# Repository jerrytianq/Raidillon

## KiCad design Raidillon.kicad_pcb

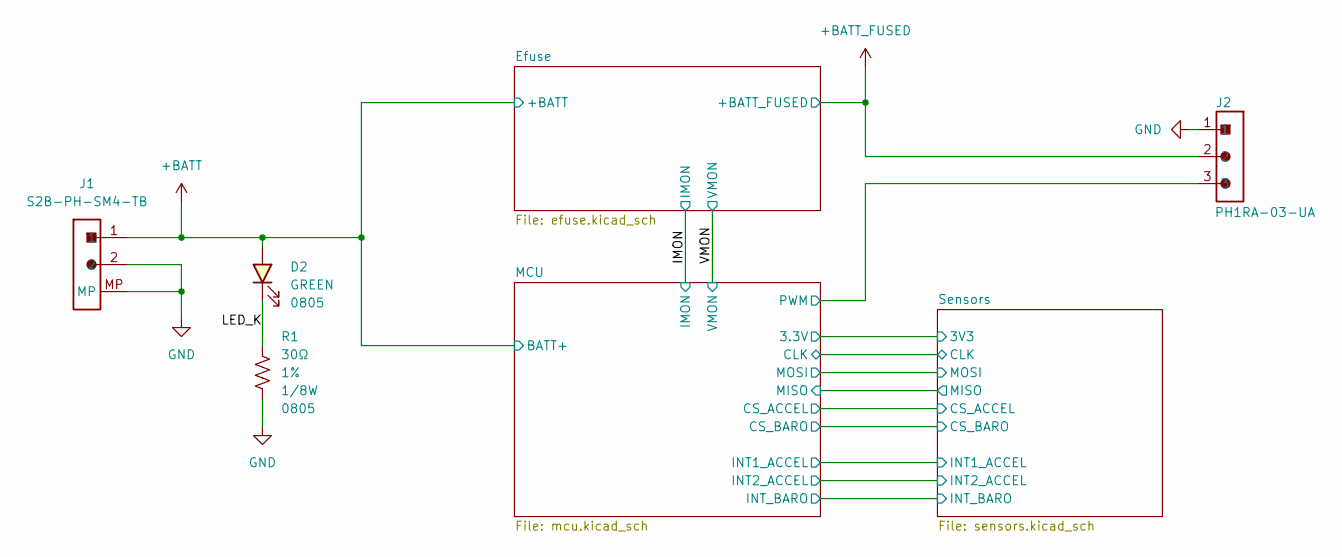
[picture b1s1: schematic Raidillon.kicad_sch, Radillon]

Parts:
D2: 150080GS75000; LED_0805_2012Metric_Pad1.15x1.40mm_HandSolder
J1: S2B-PH-SM4-TB; JST_PH_S2B-PH-SM4-TB_1x02-1MP_P2.00mm_Horizontal
J2: PH1RA-03-UA; PinHeader_1x03_P2.54mm_Horizontal
R1: RC0805FR-0730RL; R_0805_2012Metric_Pad1.20x1.40mm_HandSolder; Tolerance 1%

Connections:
+BATT: D2.2 (A), J1.1; also elsewhere on the board
+BATT_FUSED: J2.2; also elsewhere on the board
/LED_K: D2.1 (K), R1.1
/MCU/PWM: J2.3; also elsewhere on the board
GND: J1.2, J1.MP, J2.1, R1.2; also elsewhere on the board

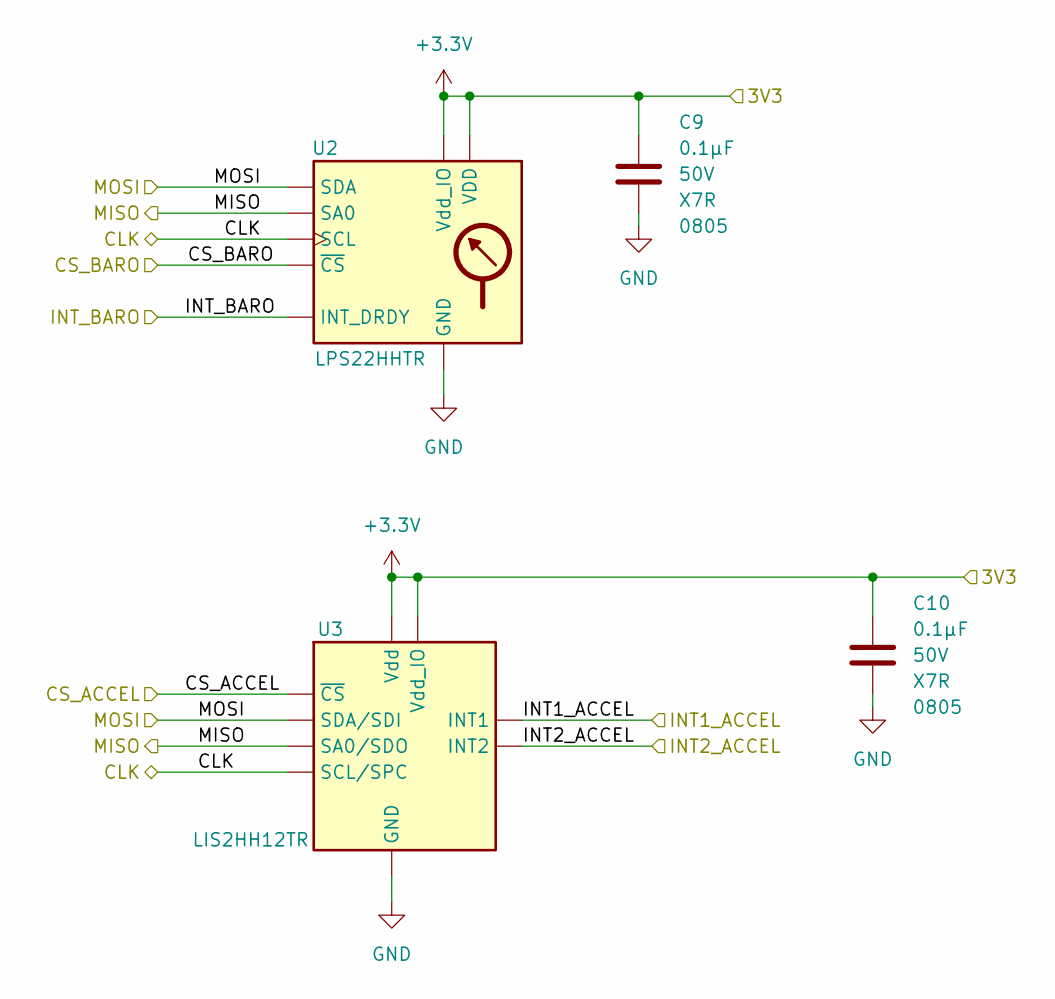
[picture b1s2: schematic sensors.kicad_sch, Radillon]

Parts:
C9, C10: CL21B104KBCNNNC; C_0805_2012Metric_Pad1.18x1.45mm_HandSolder; Rated Voltage 50V
U2: LPS22HHTR; ST_HLGA-10_LPS22HHTR
U3: LIS2HH12TR; LGA-12_LIS2HH12TR

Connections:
+3.3V: C9.1, C10.1, U2.1 (Vdd_IO), U2.10 (VDD), U3.9 (Vdd), U3.10 (Vdd_IO); also elsewhere on the board
/MCU/CLK: U2.2 (SCL), U3.1 (SCL/SPC); also elsewhere on the board
/MCU/CS_ACCEL: U3.2 (~CS); also elsewhere on the board
/MCU/CS_BARO: U2.6 (~CS); also elsewhere on the board
/MCU/INT1_ACCEL: U3.12 (INT1); also elsewhere on the board
/MCU/INT2_ACCEL: U3.11 (INT2); also elsewhere on the board
/MCU/INT_BARO: U2.7 (INT_DRDY); also elsewhere on the board
/MCU/MISO: U2.5 (SA0), U3.3 (SA0/SDO); also elsewhere on the board
/MCU/MOSI: U2.4 (SDA), U3.4 (SDA/SDI); also elsewhere on the board
GND: C9.2, C10.2, U2.3 (GND), U2.8 (GND), U2.9 (GND), U3.5 (RES), U3.6 (GND), U3.7 (GND), U3.8 (GND); also elsewhere on the board

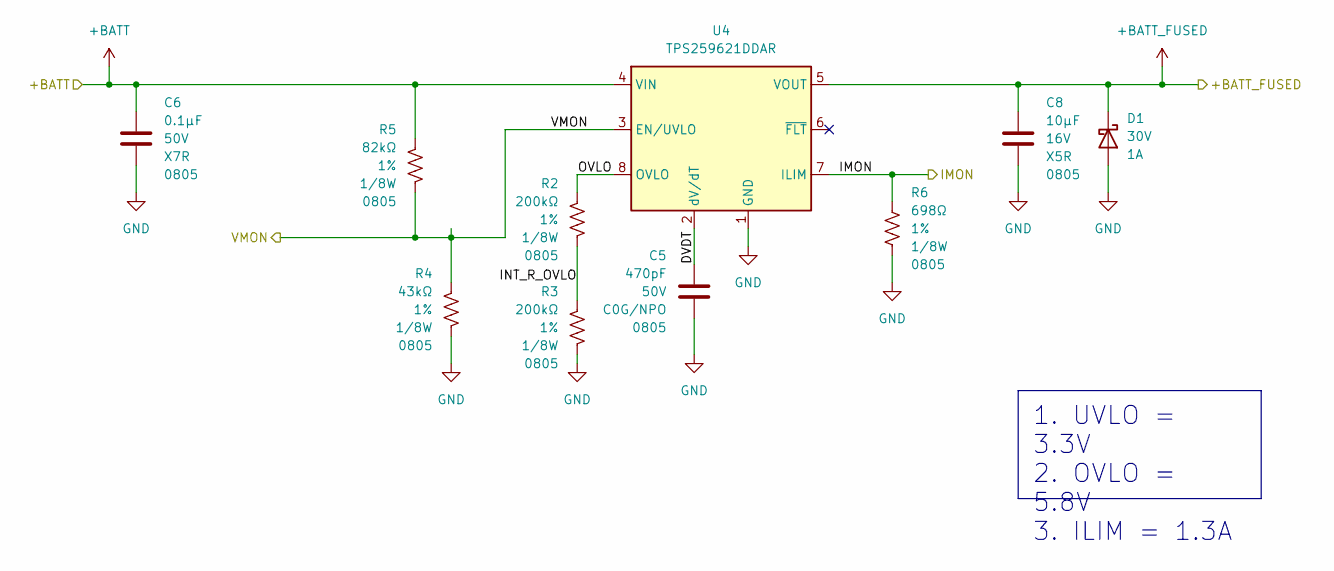
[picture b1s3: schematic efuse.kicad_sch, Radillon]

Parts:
C5: CC0805JRNPO9BN471; C_0805_2012Metric_Pad1.18x1.45mm_HandSolder; Rated Voltage 50V
C6: CL21B104KBCNNNC; C_0805_2012Metric_Pad1.18x1.45mm_HandSolder; Rated Voltage 50V
C8: GRM21BR61C106KE15K; C_0805_2012Metric_Pad1.18x1.45mm_HandSolder; Rated Voltage 16V
D1: MSS1P3L-M3/89A; D_MicroSMP_AK_MSS1P3L-M3_89A; Voltage - DC Reverse (V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 30V
R2, R3: RC0805FR-07200KL; R_0805_2012Metric_Pad1.20x1.40mm_HandSolder; Tolerance 1%
R4: RC0805FR-0743KL; R_0805_2012Metric_Pad1.20x1.40mm_HandSolder; Tolerance 1%
R5: RC0805FR-0782KL; R_0805_2012Metric_Pad1.20x1.40mm_HandSolder; Tolerance 1%
R6: RC0805FR-07698RL; R_0805_2012Metric_Pad1.20x1.40mm_HandSolder; Tolerance 1%
U4: TPS259621DDAR; SOIC-8-TPS259631DDAR; Voltage - Input 2.7V ~ 19V

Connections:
+BATT: C6.1, R5.1, U4.4 (VIN); also elsewhere on the board
+BATT_FUSED: C8.1, D1.1 (K), U4.5 (VOUT); also elsewhere on the board
/Efuse/DVDT: C5.1, U4.2 (dV/dT)
/Efuse/INT_R_OVLO: R2.2, R3.1
/Efuse/OVLO: R2.1, U4.8 (OVLO)
/IMON: R6.1, U4.7 (ILIM); also elsewhere on the board
/VMON: R4.1, R5.2, U4.3 (EN/UVLO); also elsewhere on the board
GND: C5.2, C6.2, C8.2, D1.2 (A), R3.2, R4.2, R6.2, U4.1 (GND), U4.9 (GND); also elsewhere on the board

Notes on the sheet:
1. UVLO = 3.3V 2. OVLO = 5.8V 3. ILIM = 1.3A

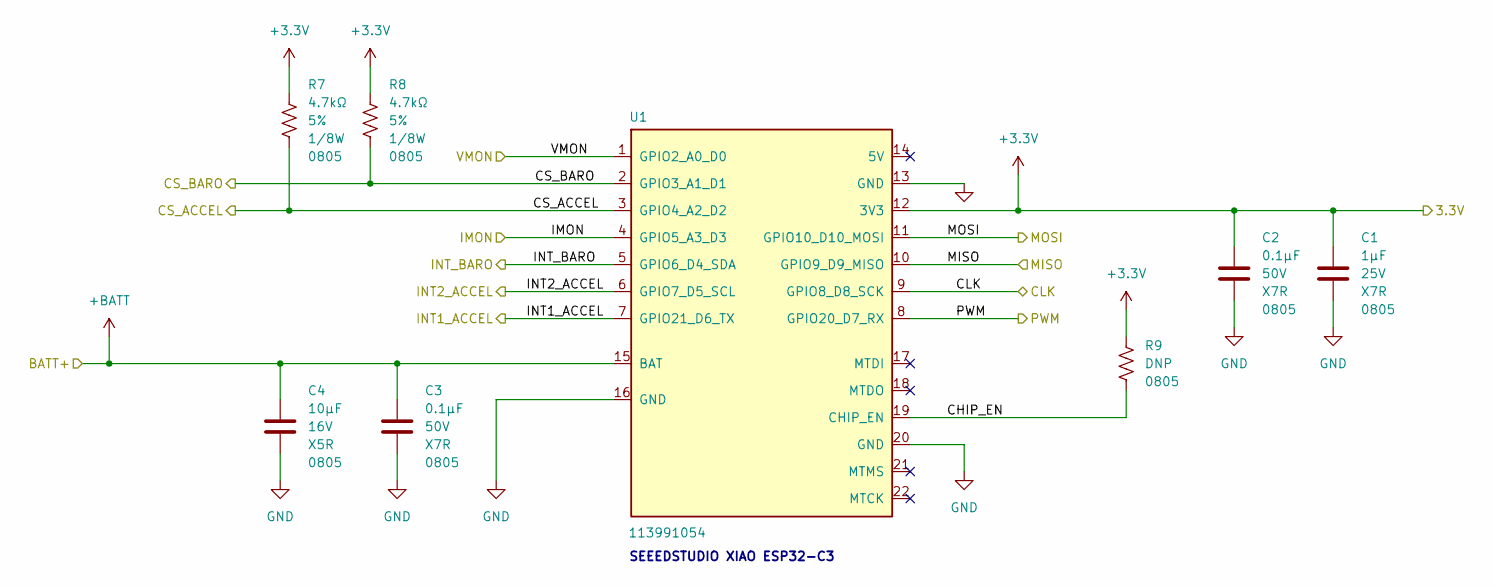
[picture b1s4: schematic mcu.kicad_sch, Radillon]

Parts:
C1: CL21B105KAFNNNE; C_0805_2012Metric_Pad1.18x1.45mm_HandSolder; Rated Voltage 25V
C2, C3: CL21B104KBCNNNC; C_0805_2012Metric_Pad1.18x1.45mm_HandSolder; Rated Voltage 50V
C4: GRM21BR61C106KE15K; C_0805_2012Metric_Pad1.18x1.45mm_HandSolder; Rated Voltage 16V
R7, R8: RMCF0805JT4K70; R_0805_2012Metric_Pad1.20x1.40mm_HandSolder; Tolerance 5%; PARTREV V.12
R9: DNP 0805; R_0805_2012Metric_Pad1.20x1.40mm_HandSolder; PARTREV V.12
U1: 113991054; XIAO-ESP32C3-SMD

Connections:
+3.3V: C1.1, C2.1, R7.1, R8.1, R9.1, U1.12 (3V3); also elsewhere on the board
+BATT: C3.1, C4.1, U1.15 (BAT); also elsewhere on the board
/IMON: U1.4 (GPIO5_A3_D3); also elsewhere on the board
/MCU/CHIP_EN: R9.2, U1.19 (CHIP_EN)
/MCU/CLK: U1.9 (GPIO8_D8_SCK); also elsewhere on the board
/MCU/CS_ACCEL: R7.2, U1.3 (GPIO4_A2_D2); also elsewhere on the board
/MCU/CS_BARO: R8.2, U1.2 (GPIO3_A1_D1); also elsewhere on the board
/MCU/INT1_ACCEL: U1.7 (GPIO21_D6_TX); also elsewhere on the board
/MCU/INT2_ACCEL: U1.6 (GPIO7_D5_SCL); also elsewhere on the board
/MCU/INT_BARO: U1.5 (GPIO6_D4_SDA); also elsewhere on the board
/MCU/MISO: U1.10 (GPIO9_D9_MISO); also elsewhere on the board
/MCU/MOSI: U1.11 (GPIO10_D10_MOSI); also elsewhere on the board
/MCU/PWM: U1.8 (GPIO20_D7_RX); also elsewhere on the board
/VMON: U1.1 (GPIO2_A0_D0); also elsewhere on the board
GND: C1.2, C2.2, C3.2, C4.2, U1.13 (GND), U1.16 (GND), U1.20 (GND); also elsewhere on the board

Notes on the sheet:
SEEEDSTUDIO XIAO ESP32-C3

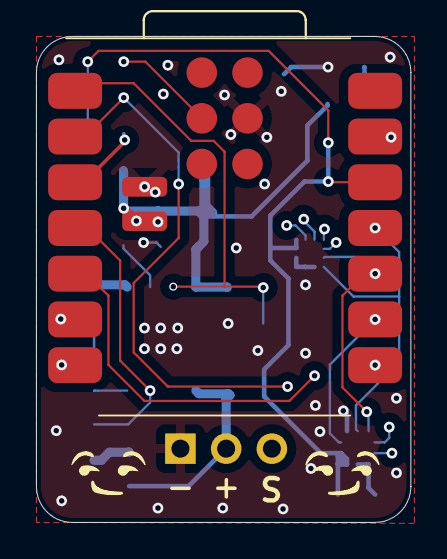
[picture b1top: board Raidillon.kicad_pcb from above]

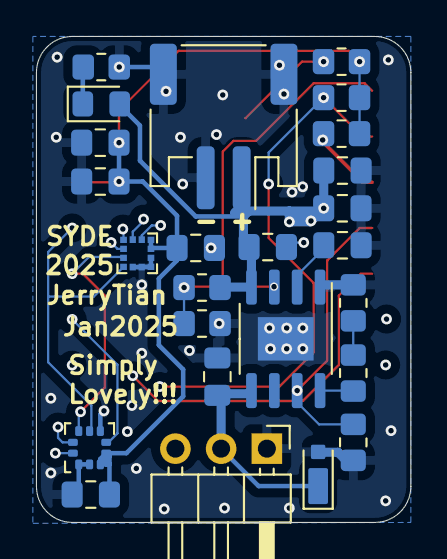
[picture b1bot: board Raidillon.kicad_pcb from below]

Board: 4 copper layers, 20.8 x 27.0 mm, 26 parts (25 on the bottom side), 20 nets.

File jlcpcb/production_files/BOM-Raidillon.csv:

Comment,Designator,Footprint,LCSC,Quantity
113991054,U1,XIAO-ESP32C3-SMD,,1
RMCF0805JT4K70,R8,R_0805_2012Metric_Pad1.20x1.40mm_HandSolder,,1
CL21B105KAFNNNE,C1,C_0805_2012Metric_Pad1.18x1.45mm_HandSolder,,1
RMCF0805JT4K70,R7,R_0805_2012Metric_Pad1.20x1.40mm_HandSolder,,1
CL21B104KBCNNNC,C9,C_0805_2012Metric_Pad1.18x1.45mm_HandSolder,,1
MSS1P3L-M3/89A,D1,D_MicroSMP_AK_MSS1P3L-M3_89A,,1
CL21B104KBCNNNC,C10,C_0805_2012Metric_Pad1.18x1.45mm_HandSolder,,1
RC0805FR-0730RL,R1,R_0805_2012Metric_Pad1.20x1.40mm_HandSolder,,1
GRM21BR61C106KE15K,C8,C_0805_2012Metric_Pad1.18x1.45mm_HandSolder,,1
GRM21BR61C106KE15K,C4,C_0805_2012Metric_Pad1.18x1.45mm_HandSolder,,1
CC0805JRNPO9BN471,C5,C_0805_2012Metric_Pad1.18x1.45mm_HandSolder,,1
150080GS75000,D2,LED_0805_2012Metric_Pad1.15x1.40mm_HandSolder,,1
CL21B104KBCNNNC,C3,C_0805_2012Metric_Pad1.18x1.45mm_HandSolder,,1
RC0805FR-0782KL,R5,R_0805_2012Metric_Pad1.20x1.40mm_HandSolder,,1
CL21B104KBCNNNC,C2,C_0805_2012Metric_Pad1.18x1.45mm_HandSolder,,1
DNP 0805,,R_0805_2012Metric_Pad1.20x1.40mm_HandSolder,,0
RC0805FR-07200KL,R2,R_0805_2012Metric_Pad1.20x1.40mm_HandSolder,,1
RC0805FR-07698RL,R6,R_0805_2012Metric_Pad1.20x1.40mm_HandSolder,,1
PH1RA-03-UA,J2,PinHeader_1x03_P2.54mm_Horizontal,,1
S2B-PH-SM4-TB,J1,JST_PH_S2B-PH-SM4-TB_1x02-1MP_P2.00mm_Horizontal,,1
LPS22HHTR,U2,ST_HLGA-10_LPS22HHTR,,1
LIS2HH12TR,U3,LGA-12_LIS2HH12TR,,1
TPS259621DDAR,U4,SOIC-8-TPS259631DDAR,,1
CL21B104KBCNNNC,C6,C_0805_2012Metric_Pad1.18x1.45mm_HandSolder,,1
RC0805FR-0743KL,R4,R_0805_2012Metric_Pad1.20x1.40mm_HandSolder,,1
RC0805FR-07200KL,R3,R_0805_2012Metric_Pad1.20x1.40mm_HandSolder,,1

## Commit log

2025-01-29 Removed duplicate pullup on chip enable resistor
2025-01-30 ordered pcb
2025-03-04 wrote code to test ldo
2025-03-12 wrote basic uart code to trigger drop mechanism
